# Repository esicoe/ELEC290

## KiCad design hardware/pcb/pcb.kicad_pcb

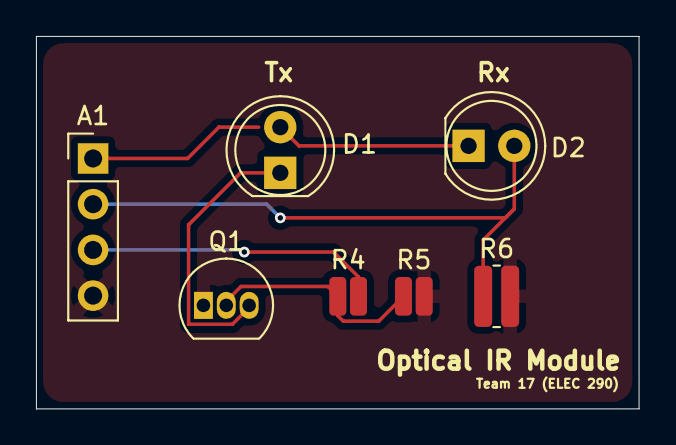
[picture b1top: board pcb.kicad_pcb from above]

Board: 2 copper layers, 33.5 x 20.7 mm, 7 parts (0 on the bottom side), 6 nets.

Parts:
A1: Arduino_Uno_R2_Shield; PinHeader_1x04_P2.54mm_Vertical
D1: VLM-940-03 LPO; LED_D5.0mm_IRBlack
D2: BPW41N; LED_D5.0mm_IRBlack
Q1: 2N7000; TO-92_Inline
R4: 100R; R_0508_1220Metric
R5: 100K; R_0508_1220Metric
R6: 47K; R_0612_1632Metric

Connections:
5V: A1.1, D1.2 (A), D2.1 (K)
/RX: A1.2, D2.2 (A), R6.1
/TX: A1.3, R4.2
GND: A1.4, Q1.1 (S), R5.2, R6.2
unnamed: D1.1 (K), Q1.3 (D)
unnamed: Q1.2 (G), R4.1, R5.1
